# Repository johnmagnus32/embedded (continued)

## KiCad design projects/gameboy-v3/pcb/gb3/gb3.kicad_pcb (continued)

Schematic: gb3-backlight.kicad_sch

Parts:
C45: 2.2µF; C0805; LCSC C125847
C46: 4.7µF; C0603; LCSC C109456
C47: 220nF; C0402; LCSC C326590
D3: SS16; SMA_L4.3-W2.6-LS5.2-RD; LCSC C2481
L2: 10µH; IND-SMD_L4.0-W4.0_LQH44PN2R2MP0L; LCSC C135263
R38: RC0402FR-075R1L; R0402; LCSC C137955
R51: 100k; R0603; LCSC C14675
TP11: TestPoint; TestPoint_Pad_D1.5mm
U6: TPS61165DBVR; SOT-23-6_L2.9-W1.6-P0.95-LS2.8-BR; LCSC C58756

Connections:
/backlight/BL_COMP: C47.1, U6.5 (COMP)
/backlight/BL_SW: D3.2 (A), L2.2, U6.3 (SW)
BL_CTRL: R51.1, U6.2 (CTRL); also elsewhere on the board
BL_LED_N: R38.1, U6.6 (FB); also elsewhere on the board
BL_LED_P: C45.1, D3.1 (K), TP11.1; also elsewhere on the board
GND: C45.2, C46.2, C47.2, R38.2, R51.2, U6.4 (GND); also elsewhere on the board
SYS: C46.1, L2.1, U6.1 (VIN); also elsewhere on the board

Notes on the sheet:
backlight

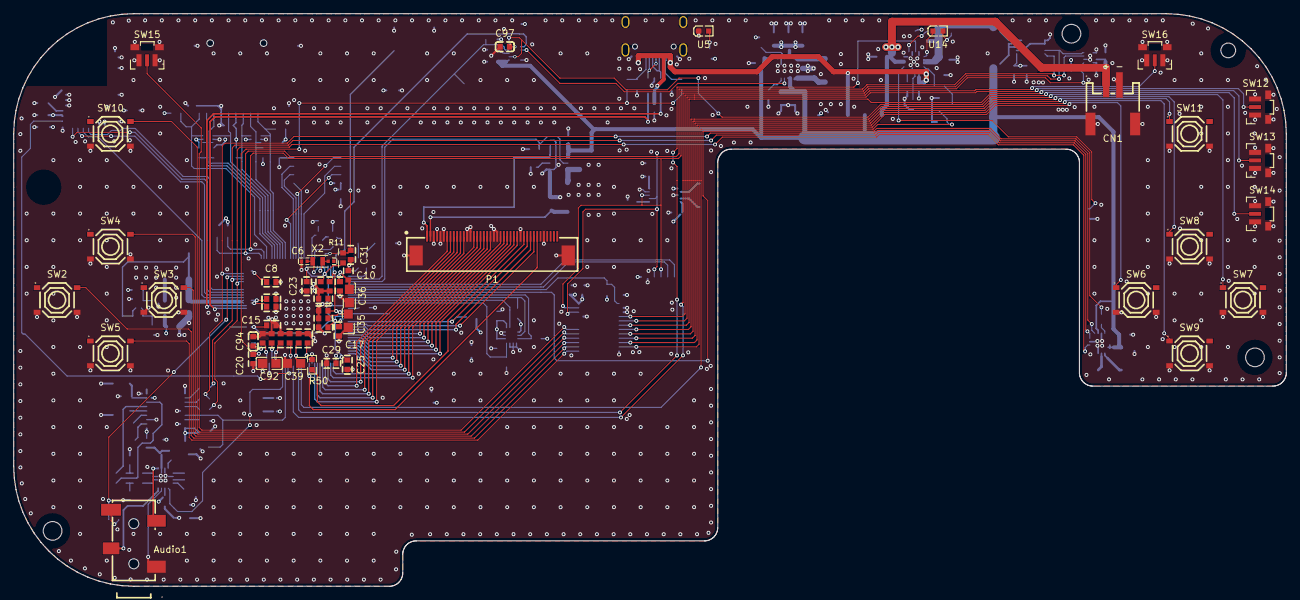
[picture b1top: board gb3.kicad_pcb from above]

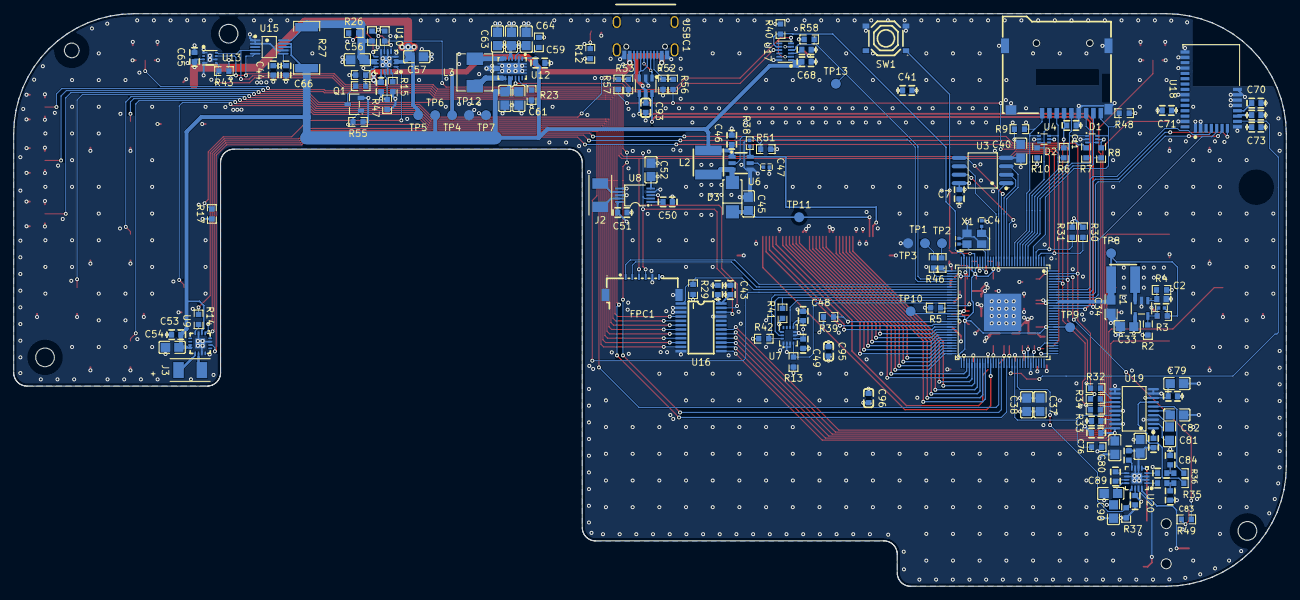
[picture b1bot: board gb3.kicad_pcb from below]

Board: 4 copper layers, 190.7 x 85.8 mm, 219 parts (159 on the bottom side), 157 nets.

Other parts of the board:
H1: MountingHole_2.2mm_M2; MountingHole_2.2x4.4mm_M2_slot
H2, H4, H5: MountingHole_2.2mm_M2; MountingHole_2.8mm_M2
H3: MountingHole_2.2mm_M2
LRA1: VG0832022D; LRA_VG0832022D
SPK1: CES-2704-088L050; SPEAKER_CES2704

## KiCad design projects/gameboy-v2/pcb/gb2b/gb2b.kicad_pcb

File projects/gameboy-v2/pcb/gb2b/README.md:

# gb2b: gb2 rev B

The KiCad project for **rev B** of gb2, the GBA-style handheld (STM32F411RE + iCE40UP5K driving the 8-bit 8080
display bus, BT830, BQ24073, TPS63021, MT3608). The design spec is **[../REVB_DESIGN.md](../REVB_DESIGN.md)**.

**Rev A (`../gb2/`) is ordered and frozen.** Never edit anything there. Rev B is a separate project that started
as a copy of it.

## What rev B changes (locked 2026-10-14)

- **Screen:** EastRising ER-TFT028A2-4 bare panel (2.8" IPS 240x320, ILI9341, no touch, 50-pin 0.5 mm FPC) replaces the
  Adafruit 2090 module. The panel is held in the front shell on a foam gasket under a 1.1 mm glass cover, with the board
  0.3 mm behind it. There are no front-side parts under the panel. The FPC folds behind the panel and joggles through a
  board opening to a top-contact 50-pin connector on the back (JUSHUO AFC07-S50ECA-00, LCSC C262650).
- **Battery:** Adafruit 258 (35 x 62 x 5 mm, 1200 mAh, JST-PH), in a portrait board cut-out left of that connector,
  behind a 0.5 mm stainless plate, with a flush battery door. The back is flat and the device is about 12.5 mm thick all round (REVB_DESIGN.md §3.1).
- **Extras:** USB D+/D- to the STM32 PA11/PA12 (DFU) with an ESD array and a VBUS TVS. J8 sits next to the charger U9.
  The IMU is kept away from screws, posts, the LRA and the speaker. The panel frame is grounded. TE goes to the FPGA
  (U2 pin 44, `LCD_TE`; REVB_DESIGN.md decision 16 moved it from the brief's pin 38 so the bus fans out without
  crossings). The FPGA drives the panel reset with a 10k pull-up. RD is tied to +3V3, IM0-3 and the unused
  inputs go to GND, and SDO is left open.

## Status

**Schematic: rev B's electrical changes are in (2026-10-14).** The PCB is not updated yet.

- `gb2b-nets.csv` / `gb2b-bom.csv` carry REVB_DESIGN.md §4-5:
  - the 50-pin FPC connector J3, with every panel pin wired;
  - the backlight driver (R32-R37, Q2; R32-R35 = 120 Ω C22787) on a new `backlight` sheet;
  - the LCD_RST pull-up R38, and C52/C53;
  - the GND pads MP1-MP8 (MP7/MP8 land the plate's copper-foil bridges);
  - USB D+/D- to PA11/PA12 through U13, with the VBUS TVS D4;
  - the right-angle SWD header J1, and the 10k reel swap;
  - the schematic-review fixes: FPGA_CDONE moved to PB0 with R39 pulling BOOT1 (PB2) low, and R25 as a PS/SYNC
    pull-up (REVB_DESIGN.md decisions 14 and 22).

  J4 is gone. BOM changes: `BOM_REVB.md`. `BOM.md` here is rev B's full machine-readable BOM (rev A's rows plus
  #84-#92), which `fab/fab.py` reads.
- The schematic regenerates with `gen.py` (below): 154 parts and 19 child sheets. The VALIDATE gate passes. ERC gives
  0 errors and 229 warnings, all of the same two kinds as rev A's 229: generator-made power symbols not found in the
  `power` library, and pin-to-pin warnings on the shared library's "unspecified" pins.
- `gb2b.kicad_pcb` is still rev A's placed and routed board, linked to the rev A parts. It still has J4 and the old J3,
  and it lacks the 21 new parts until "Update PCB from Schematic" (or `place.py`) runs in the placement step
  (REVB_DESIGN.md §9 step 3). `route/groups/` was deliberately **not** copied.
- These files still describe rev A and get revised as rev B lands:
  - `mech_ref.json` + `draw_mech.py` (the 2090 module and the Adafruit 2011 cell);
  - `route/PLAN.md` and `route/channels.py` (rev A's corridors);
  - `fab/verify.py` (checks J3/J4 against the 2090);
  - `fab/fab.py`'s checklist notes (J1, J3, J8). Its BOM lookup now reads `BOM.md` in this directory and stops on an
    unknown `#N`.

## Layout

| Path | What |
|---|---|
| `gb2b.kicad_pro` / `.kicad_sch` / `sheets/gb2b-*.kicad_sch` | Project + generated hierarchical schematic (one child sheet per subcircuit) |
| `gb2b.kicad_pcb`, `gb2b.kicad_dru` | Board + custom DRC rules |
| `gb2b-bom.csv`, `gb2b-nets.csv` | **The schematic source.** Edit these, never the .kicad_sch |
| `lib/gb2b.kicad_sym`, `lib/gb2b.pretty/`, `lib/gb2b.3dshapes/` | Project-local library (nickname `gb2b`) for rev B's new symbols and footprints. `../../../../cad/symbols` holds shared work, so rev B parts don't go there |
| `gen.py` | Runs the schematic generator with the project-local library |
| `BOM_REVB.md` | Rev B's BOM delta against rev A (LCSC, tier, stock) and the footprint checks |
| `BOM.md` | Rev B's full BOM rows (rev A's + #84-#92), the `#N` lookup `fab/fab.py` uses |
| `title.py` | Stamps the "gb2 rev B" title block into every sheet + the board |
| `place.py` | Schematic -> board import + placement |
| `route/` | Routing + check tools (fanout, pour, silk, audit, IPC current, I2C rise time, plane return path, plot) |
| `fab/fab.py`, `fab/verify.py` | JLC outputs (into `fab/out/`, git-ignored) + the pre-fab checks |

## Regenerating the schematic

Close KiCad first, then from the repo root:

```sh
python3 projects/gameboy-v2/pcb/gb2b/gen.py       # = cad/generate_schematic.py + the gb2b library, on this dir's CSVs
python3 projects/gameboy-v2/pcb/gb2b/title.py     # the generator writes no title block
```

`gen.py` wraps the shared generator without changing it. The generator itself only loads `easyeda2kicad` and `manual`
from one `--symbols` directory, so the wrapper also loads `lib/gb2b.kicad_sym`. Pass `--project <copy>` for a dry run
into a copy at the same folder depth.

The generator's VALIDATE gate (ERC 0 errors, netlist partition match) must say PASS.

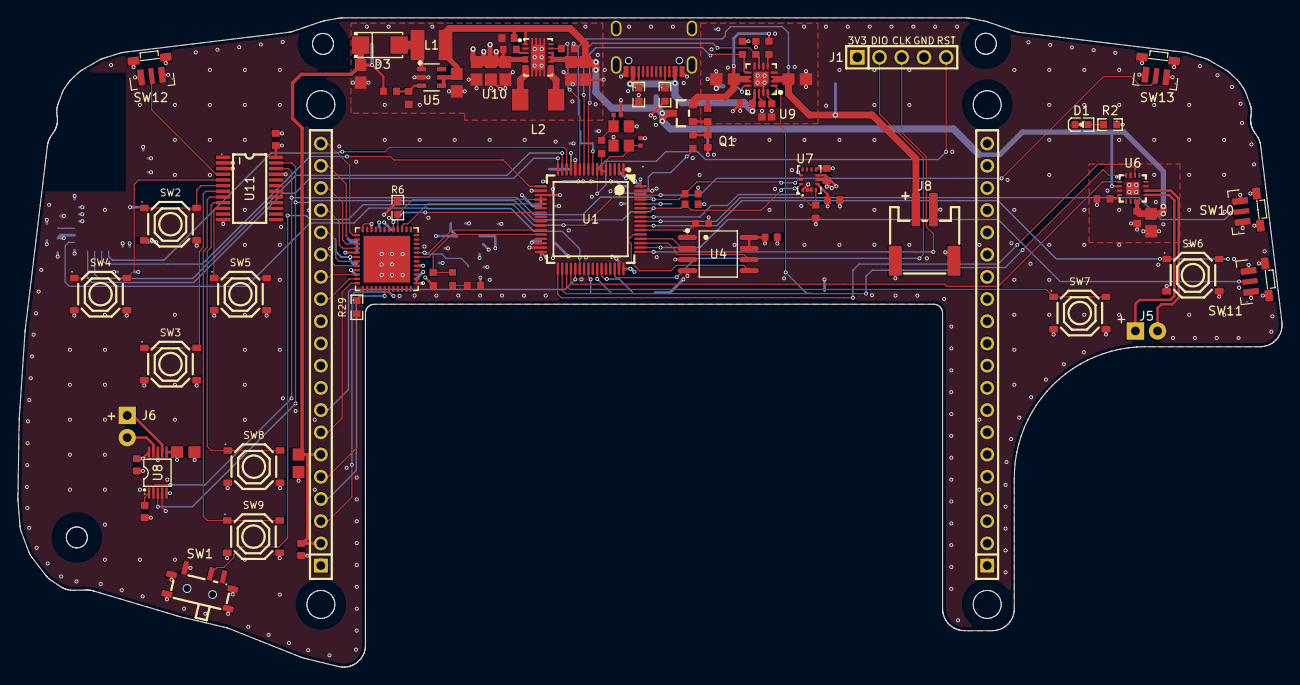
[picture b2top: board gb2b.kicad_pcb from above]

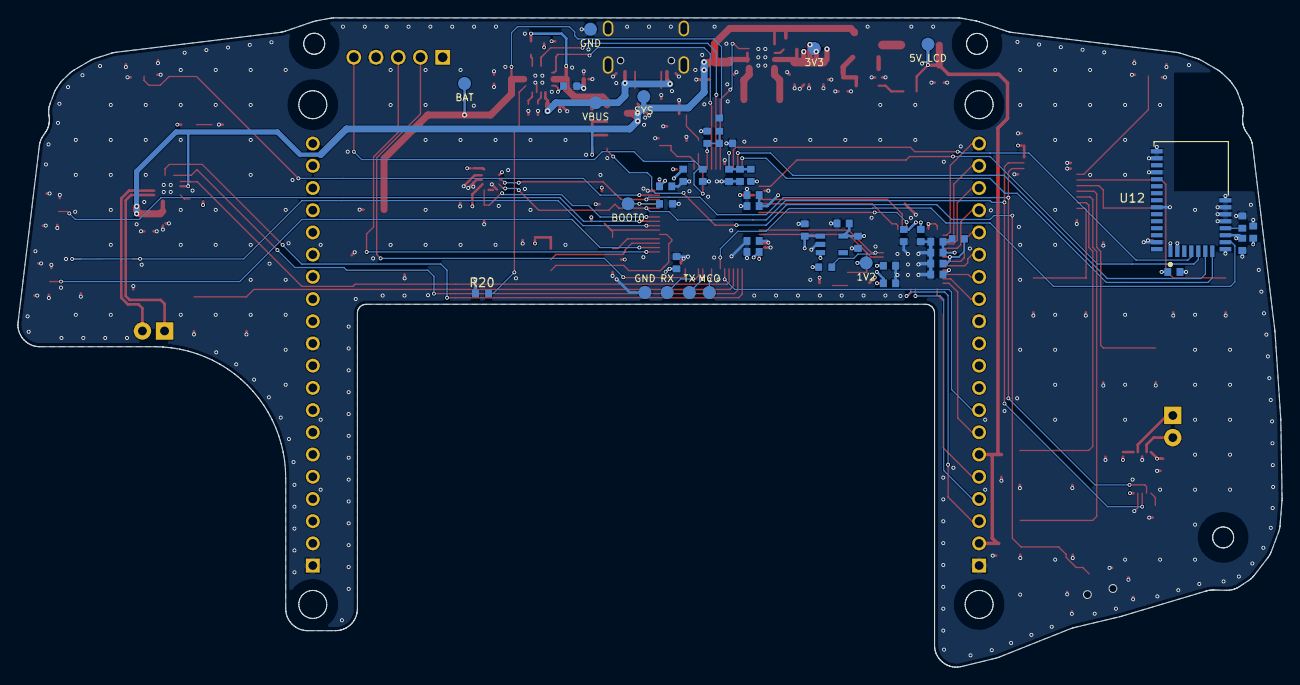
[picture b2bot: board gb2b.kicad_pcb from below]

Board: 4 copper layers, 144.6 x 74.2 mm, 134 parts (48 on the bottom side), 94 nets.

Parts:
C1, C2, C3, C4, C5, C6, C13, C14, C15, C16, C17, C18, C19, C24, C25, C29, C31, C32, C34, C39, C45, C46, C48, C49, C51: 100nF; C0603
C7, C8, C20, C21, C22, C23, C36, C47, C50: 4.7µF; C0603
C9: 10nF; C0603
C10, C33: 1µF; C0603
C11, C12: 15pF; C0402
C26, C27, C30, C35, C37, C38, C40, C41: 10µF; C0805
C28, C42, C43, C44: 22µF; C0805
D1, D2: 19-213SYGC/S530-E2/5T; LED0603-RD
D3: SS34_C8678; SMA_L4.3-W2.6-LS5.2-RD
FB1, FB2: 600Ω; L0603
J1: MTP125-1105S1; HDR-TH_5P-P2.54-V-M
J3, J4: HX PM2.54-1X20P ZC; PinSocket_1x20_P2.54_D1.0
J5, J6: SolderPad_1x02
J7: TYPE-C-31-M-12; USB-C_SMD-TYPE-C-31-M-12_1
J8: S2B-PH-SM4-TB; CONN-SMD_P2.00_S2B-PH-SM4-TB-LF-SN
L1: 4.7µH; IND-SMD_L4.0-W4.0
L2: 1.5µH; IND-SMD_L5.4-W5.2
Q1: AO3401A; SOT-23_L2.9-W1.3-P1.90-LS2.4-BR
R1, R4, R5, R8, R10, R12, R20, R22, R23, R31: 10k; R0603
R2, R7: 510Ω; R0603
R3, R17, R24: 0Ω; R0603
R6, R19: 3.3k; R0603
R9: 73.2k; R0603
R11: 620k; R0603
R13, R14: 1.5k; R0603
R15, R16: 5.1k; R0603
R18: 2k; R0603
R21: 68k; R0603
R25, R26, R27, R30: 100k; R0603
R29: 33Ω; R0603
SW1: MSK12C02-HB; SW-TH_MSK12C02-HB-1
SW2, SW3, SW4, SW5, SW6, SW7, SW8, SW9: TS-1187A-B-A-B; SW-SMD_4P-L5.1-W5.1-P3.70-LS6.5-TL_H1.5
SW10, SW11, SW12, SW13: SKRTLBE010; KEY-SMD_SKRTLAE010-1
TP1, TP2, TP3, TP4, TP5, TP6, TP7, TP8, TP9, TP10, TP11, TP12: TestPoint; TestPoint_Pad_D1.5mm
U1: STM32F411RET6; LQFP-64_L10.0-W10.0-P0.50-LS12.0-BL
U2: ICE40UP5K-SG48I; QFN-48_L7.0-W7.0-P0.50-TL-EP5.4-1
U3: AP2127K-1.2TRG1; SOT-23-5_L3.0-W1.7-P0.95-LS2.8-BR
U4: W25Q128JVSIQTR; SOIC-8_L5.3-W5.3-P1.27-LS8.0-BL
U5: MT3608; SOT-23-6_L2.9-W1.6-P0.95-LS2.8-BL
U6: MAX98357AETE+T; TQFN-16_L3.0-W3.0-P0.50-BL-EP1.5
U7: LSM6DSOXTR; LGA-14L_L3.0-W2.5-P0.50-TL
U8: DRV2605LDGSR; VSSOP-10_L3.0-W3.0-P0.50-LS4.9-BL
U9: BQ24073RGTR; QFN-16_L3.0-W3.0-P0.50-TL-EP1.7
U10: TPS63021DSJR; VSON-14_L4.0-W3.0-P0.50-BL-EP_TI_DSJ
U11: PCA9555PWR; TSSOP-24_L7.8-W4.4-P0.65-LS6.4-BL
U12: BT830-SA-01-T_R; XCVR_BT830-SA-01-T_R
Y1: DSX321G 8MHz; CRYSTAL-SMD_4P-L3.2-W2.5-BL-1

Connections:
+1V2: C13.1, C14.1, C22.1, C23.1, FB2.1, TP7.1, U2.5, U2.30, U3.5
+1V2_PLL: C19.1, C20.1, FB2.2, U2.29
+3V3: C1.1, C2.1, C3.1, C4.1, C5.1, C8.1, C15.1, C16.1, C17.1, C18.1, C21.1, C24.1, C31.1, C32.1, C34.1, C35.1, C42.1, C43.1, C44.1, C46.1, C48.1, C49.1, C50.1, FB1.1, J1.1, R2.1, R4.2, R5.2, R7.1, R8.2, R11.2, R13.2, R14.2, R22.2, R23.2, R24.2, TP5.1, U1.1, U1.19, U1.32, U1.48, U1.64, U2.1, U2.22, U2.24, U2.33, U3.1, U3.3, U4.3, U4.7, U4.8, U7.5, U7.8, U7.12, U8.5, U8.6, U8.10, U10.4, U10.5, U11.24, U12.1, U12.9
+3V3A: C9.1, C10.1, FB1.2, U1.13
+5V_LCD: C25.1, C26.1, C28.1, D3.1, J3.2, J3.6, R9.1, TP6.1
/amp/AMP_SD_MODE: R11.1, U6.4
/amp/SPK_N: J5.2, U6.10
/amp/SPK_P: J5.1, U6.9
/bluetooth/BT_VREG18: C47.1, U12.10
/buck-boost/BB_FB: R24.1, U10.3
/buck-boost/BB_L1: L2.1, U10.8, U10.9
/buck-boost/BB_L2: L2.2, U10.6, U10.7
/charger/CHG_EN2: R17.1, U9.5
/charger/CHG_ILIM: R19.1, U9.12
/charger/CHG_ISET: R18.1, U9.16
/charger/CHG_TMR: R21.1, U9.14
/charger/CHG_TS: R20.1, U9.1
/charger/PWR_SW: R31.1, SW1.2
/charger/Q1_GATE: C51.1, Q1.1, R30.1, R31.2
/clock/HSE_OUT: C12.1, R3.2, Y1.3
/fpga/CDONE_LED_A: D2.2, R7.2
/fpga/LCD_WR_FPGA: R29.1, U2.37
/haptics/HAP_REG: C33.1, U8.1
/haptics/LRA_N: J6.2, U8.9
/haptics/LRA_P: J6.1, U8.7
/lcd-boost/BST_FB: R9.2, R10.1, U5.3
/lcd-boost/BST_SW: D3.2, L1.2, U5.1
/mcu/BOOT0: R1.1, TP8.1, U1.60
/mcu/MCO2: TP9.1, U1.40
/mcu/NRST: C6.1, J1.5, U1.7
/mcu/PWR_LED_A: D1.2, R2.2
/mcu/SWCLK: J1.3, U1.49
/mcu/SWDIO: J1.2, U1.46
/mcu/USART1_RX: TP12.1, U1.43
/mcu/USART1_TX: TP11.1, U1.42
/mcu/VCAP1: C7.1, U1.30
/usb-c/USBC_CC1: J7.A5, R15.1
/usb-c/USBC_CC2: J7.B5, R16.1
BAT: C38.1, J8.1, R26.1, TP2.1, U9.2, U9.3
BAT_SENSE: C45.1, R26.2, R27.1, U1.8
BB_PSYNC: R25.1, U1.11, U10.13
BTN_A: SW6.1, SW6.2, U1.55
BTN_B: SW7.1, SW7.2, U1.35
BTN_DOWN: SW3.1, SW3.2, U11.7
BTN_L: SW12.2, U11.4
BTN_LEFT: SW4.1, SW4.2, U11.5
BTN_R: SW13.2, U1.62
BTN_RIGHT: SW5.1, SW5.2, U11.10
BTN_SELECT: SW9.1, SW9.2, U11.8
BTN_START: SW8.1, SW8.2, U11.9
BTN_UP: SW2.1, SW2.2, U11.6
BTN_VOLDOWN: SW11.2, U1.50
BTN_VOLUP: SW10.2, U1.56
BT_EN: U1.38, U12.8
CHG_PGOOD: R23.1, U1.10, U9.7
CHG_STAT: R22.1, U1.9, U9.9
FPGA_CDONE: D2.1, R5.1, U1.28, U2.7
FPGA_CRESET_B: R4.1, U1.27, U2.8
FPGA_SS_B: R6.1, U1.20, U2.16
GND: C1.2, C2.2, C3.2, C4.2, C5.2, C6.2, C7.2, C8.2, C9.2, C10.2, C11.2, C12.2, C13.2, C14.2, C15.2, C16.2, C17.2, C18.2, C19.2, C20.2, C21.2, C22.2, C23.2, C24.2, C25.2, C26.2, C27.2, C28.2, C29.2, C30.2, C31.2, C32.2, C33.2, C34.2, C35.2, C36.2, C37.2, C38.2, C39.2, C40.2, C41.2, C42.2, C43.2, C44.2, C45.2, C46.2, C47.2, C48.2, C49.2, C50.2, D1.1, J1.4, J3.1, J3.12, J4.1, J4.11, J7.1, J7.2, J7.3, J7.4, J7.A1B12, J7.B1A12, J8.2, J8.3, J8.4, R1.2, R6.2, R10.2, R12.2, R15.2, R16.2, R18.2, R19.2, R20.2, R21.2, R25.2, R27.2, SW1.1, SW1.4, SW2.3, SW2.4, SW3.3, SW3.4, SW4.3, SW4.4, SW5.3, SW5.4, SW6.3, SW6.4, SW7.3, SW7.4, SW8.3, SW8.4, SW9.3, SW9.4, SW10.1, SW10.3, SW10.4, SW10.5, SW11.1, SW11.3, SW11.4, SW11.5, SW12.1, SW12.3, SW12.4, SW12.5, SW13.1, SW13.3, SW13.4, SW13.5, TP4.1, TP10.1, U1.12, U1.18, U1.31, U1.47, U1.63, U2.49, U3.2, U4.4, U5.2, U6.3, U6.11, U6.15, U6.17, U7.1, U7.2, U7.3, U7.6, U7.7, U8.4, U8.8, U9.4, U9.6, U9.8, U9.15, U9.17, U10.2, U10.15, U11.2, U11.3, U11.12, U11.21, U12.2, U12.11, U12.12, U12.13, U12.14, U12.15, U12.16, U12.18, U12.23, U12.28, U12.30, Y1.2, Y1.4
HSE_IN: C11.1, U1.5, Y1.1
HSE_OUT_MCU: R3.1, U1.6
I2C1_SCL: R13.1, U1.61, U7.13, U8.2, U11.22
I2C1_SDA: R14.1, U1.59, U7.14, U8.3, U11.23
I2S2_CK: U1.34, U6.16
I2S2_SD: U1.36, U6.1
I2S2_WS: U1.33, U6.14
IMU_INT1: R12.1, U1.57, U7.4
LCD_CS: J3.3, U2.43
LCD_D0: J3.13, U2.35
LCD_D1: J3.14, U2.34
LCD_D2: J3.15, U2.32
LCD_D3: J3.16, U2.31
LCD_D4: J3.17, U2.28
LCD_D5: J3.18, U2.27
LCD_D6: J3.19, U2.26
LCD_D7: J3.20, U2.25
LCD_DC: J3.4, U2.42
LCD_LITE: J3.8, U1.37
LCD_RST: J3.7, U2.36
LCD_WR: J3.5, R29.2
NOR_CS: R8.1, U1.54, U4.1
PPU_SPI_MOSI: U1.23, U2.17
PPU_SPI_SCK: U1.21, U2.15
SPI3_MISO: U1.52, U4.2
SPI3_MOSI: U1.53, U4.5
SPI3_SCK: U1.51, U4.6
SYS: C27.1, C29.1, C30.1, C39.1, C40.1, C41.1, C51.2, L1.1, Q1.3, TP3.1, U5.4, U5.5, U6.2, U6.7, U6.8, U10.1, U10.10, U10.11, U10.12
SYS_SRC: C37.1, Q1.2, R17.2, R30.2, U9.10, U9.11
USART2_CTS: U1.14, U12.4
USART2_RTS: U1.15, U12.6
USART2_RX: U1.17, U12.5
USART2_TX: U1.16, U12.7
VBUS: C36.1, J7.A4B9, J7.B4A9, TP1.1, U9.13

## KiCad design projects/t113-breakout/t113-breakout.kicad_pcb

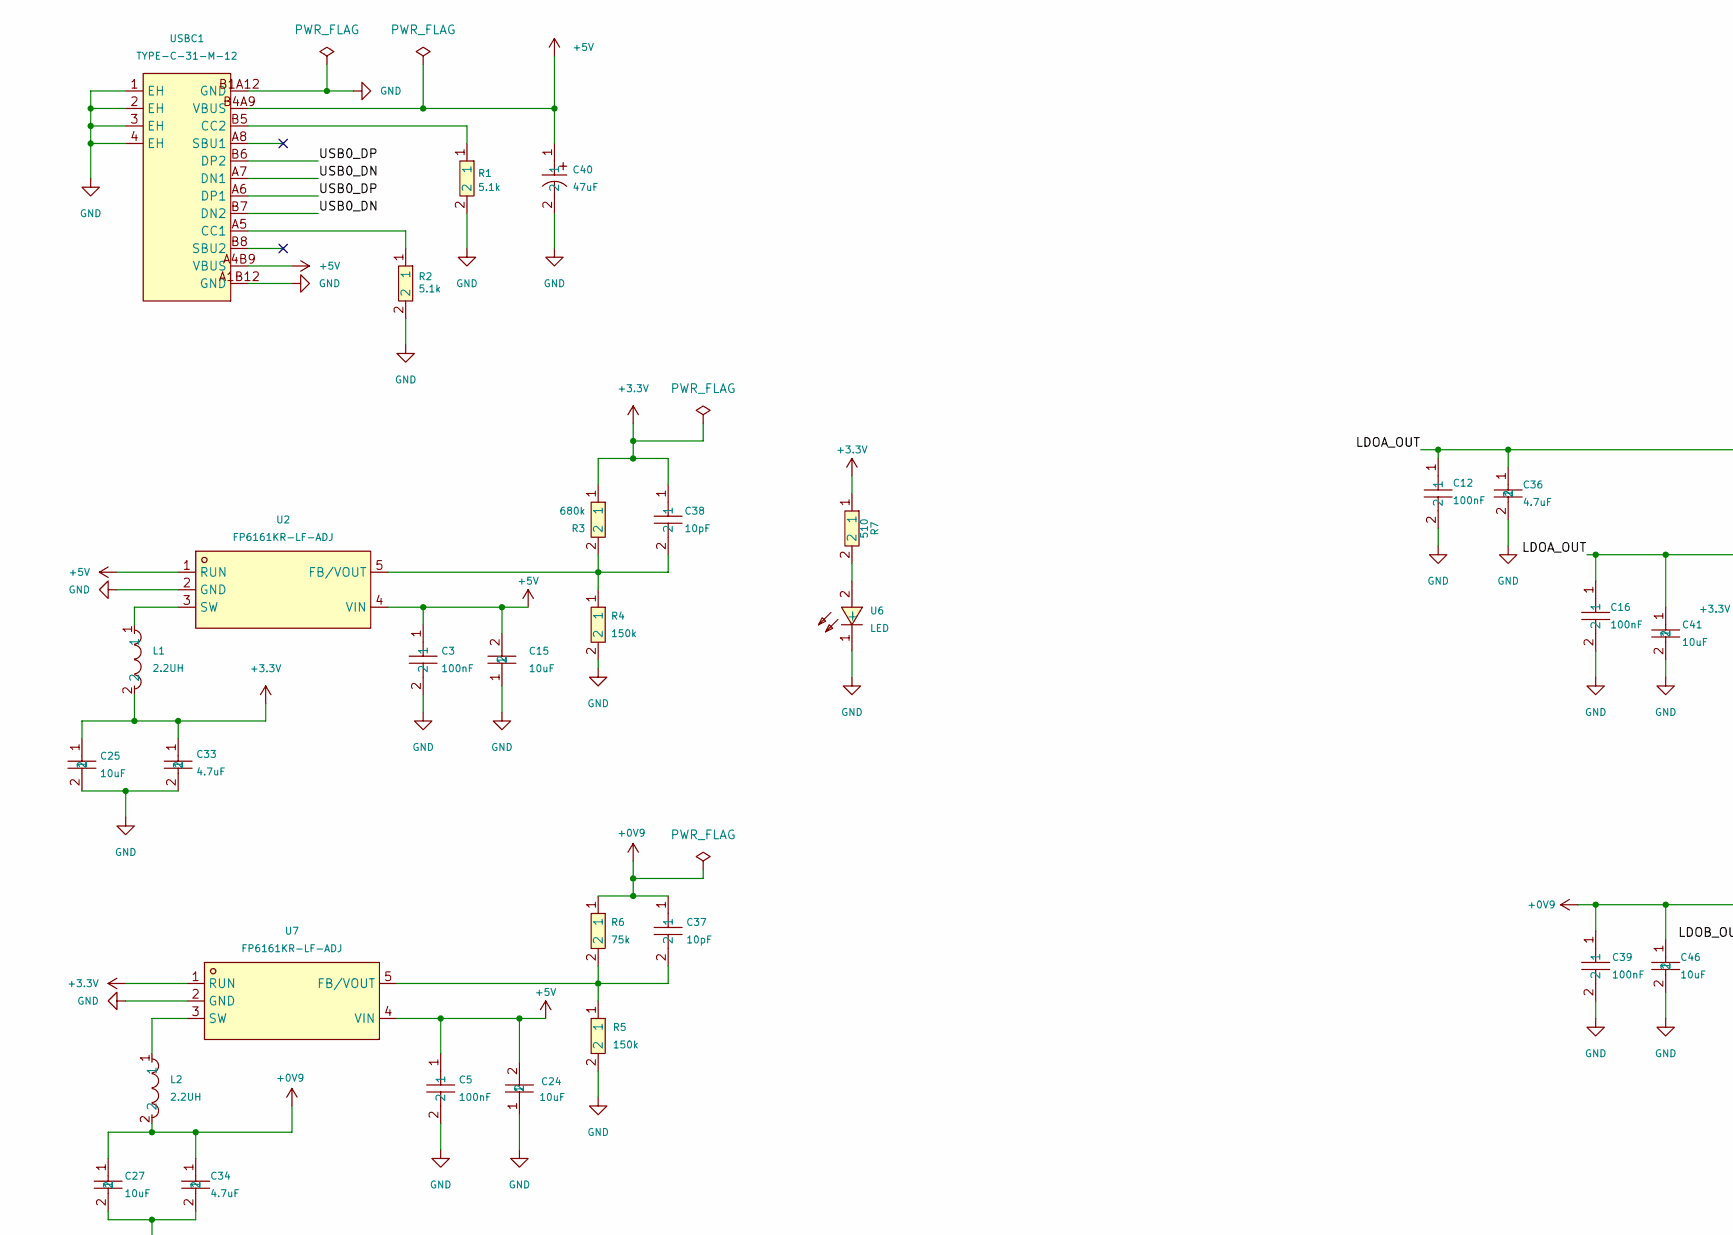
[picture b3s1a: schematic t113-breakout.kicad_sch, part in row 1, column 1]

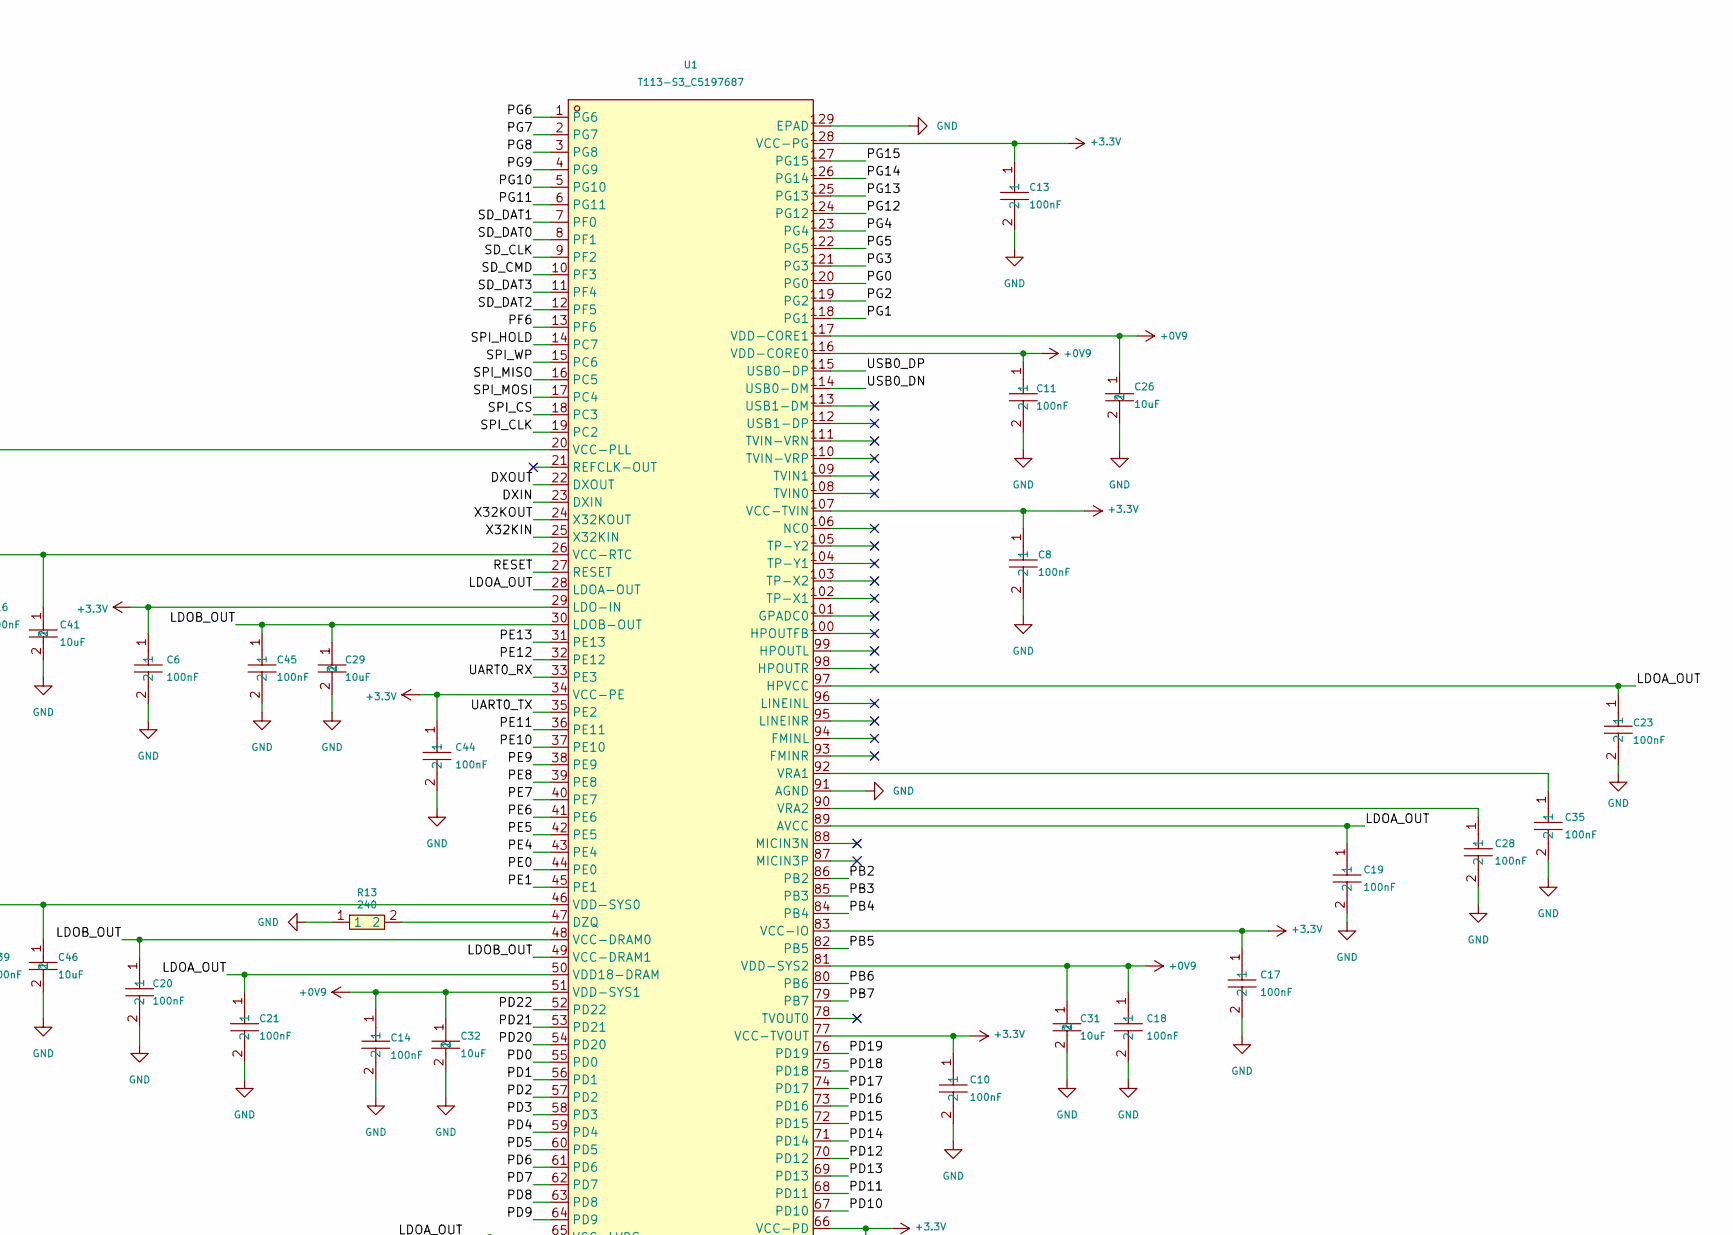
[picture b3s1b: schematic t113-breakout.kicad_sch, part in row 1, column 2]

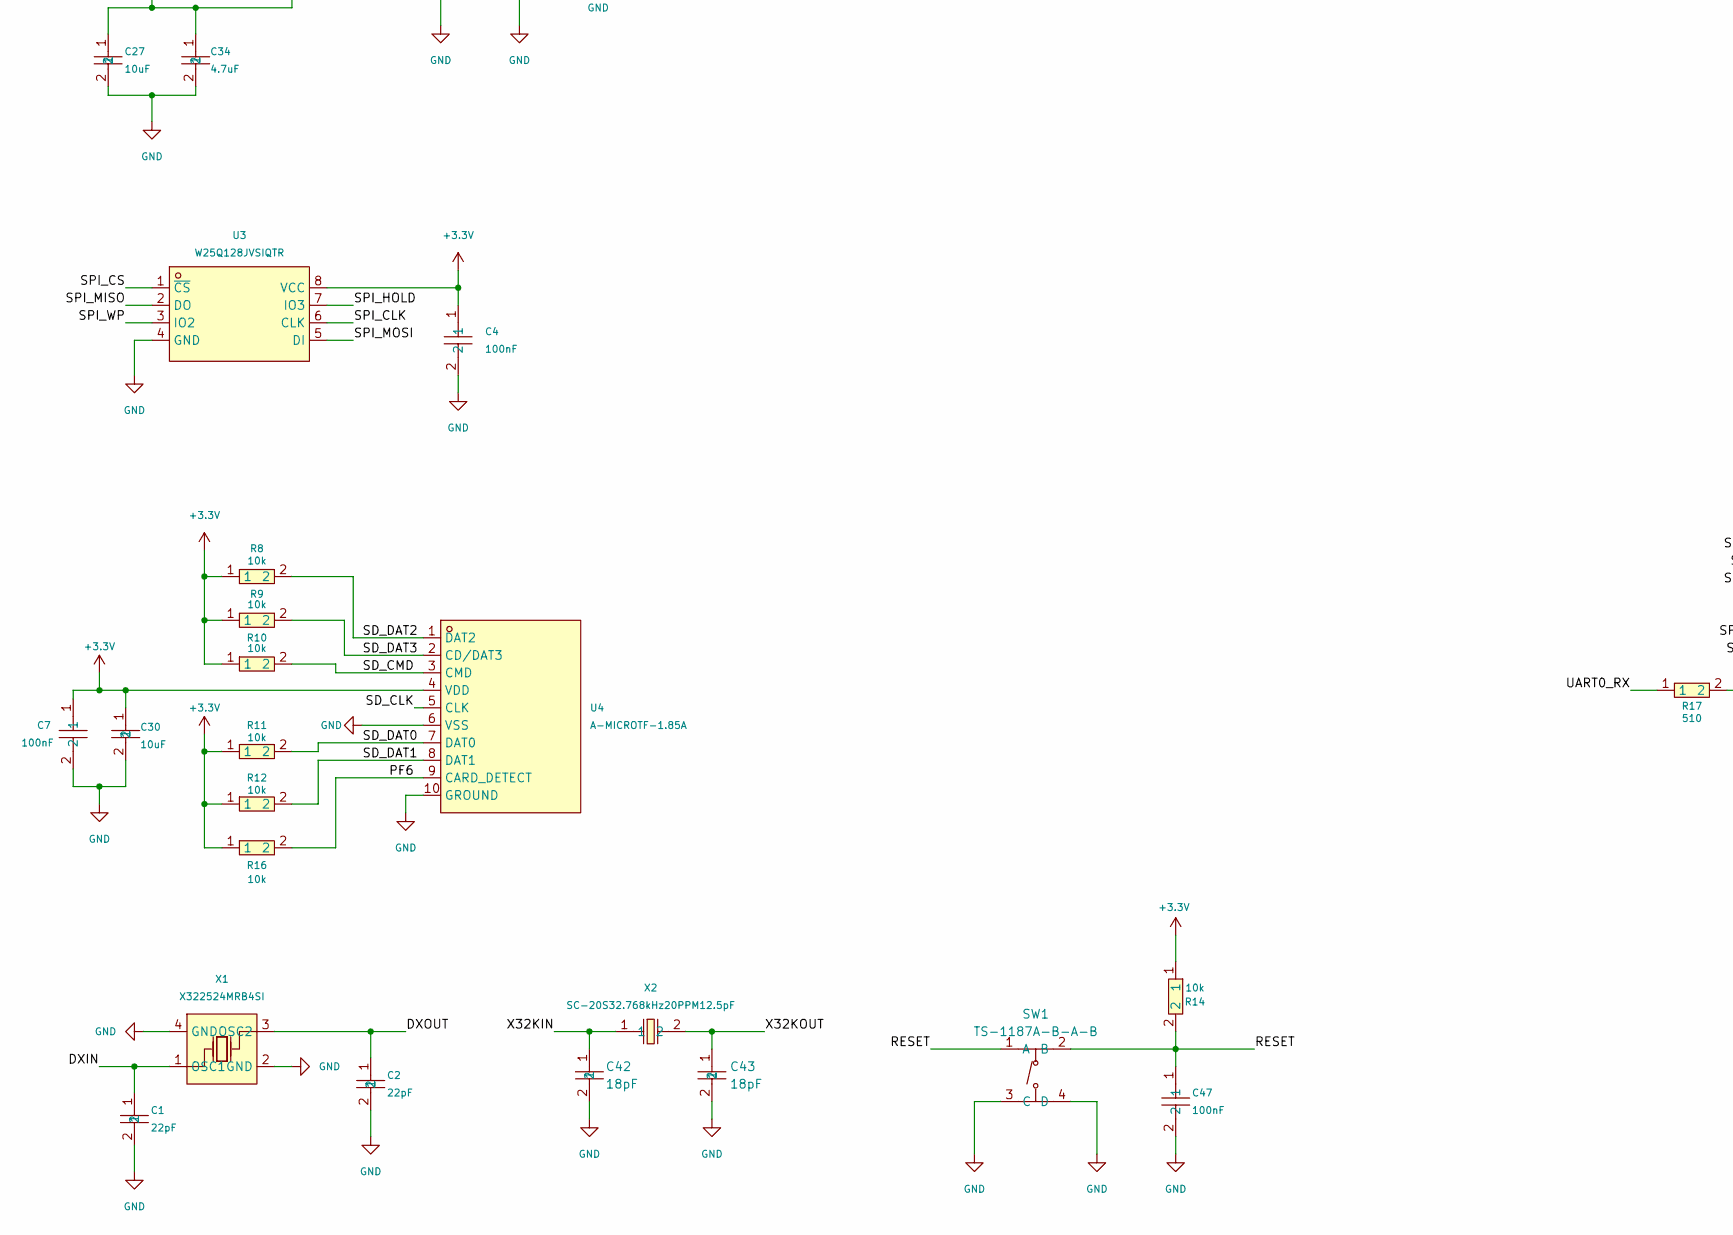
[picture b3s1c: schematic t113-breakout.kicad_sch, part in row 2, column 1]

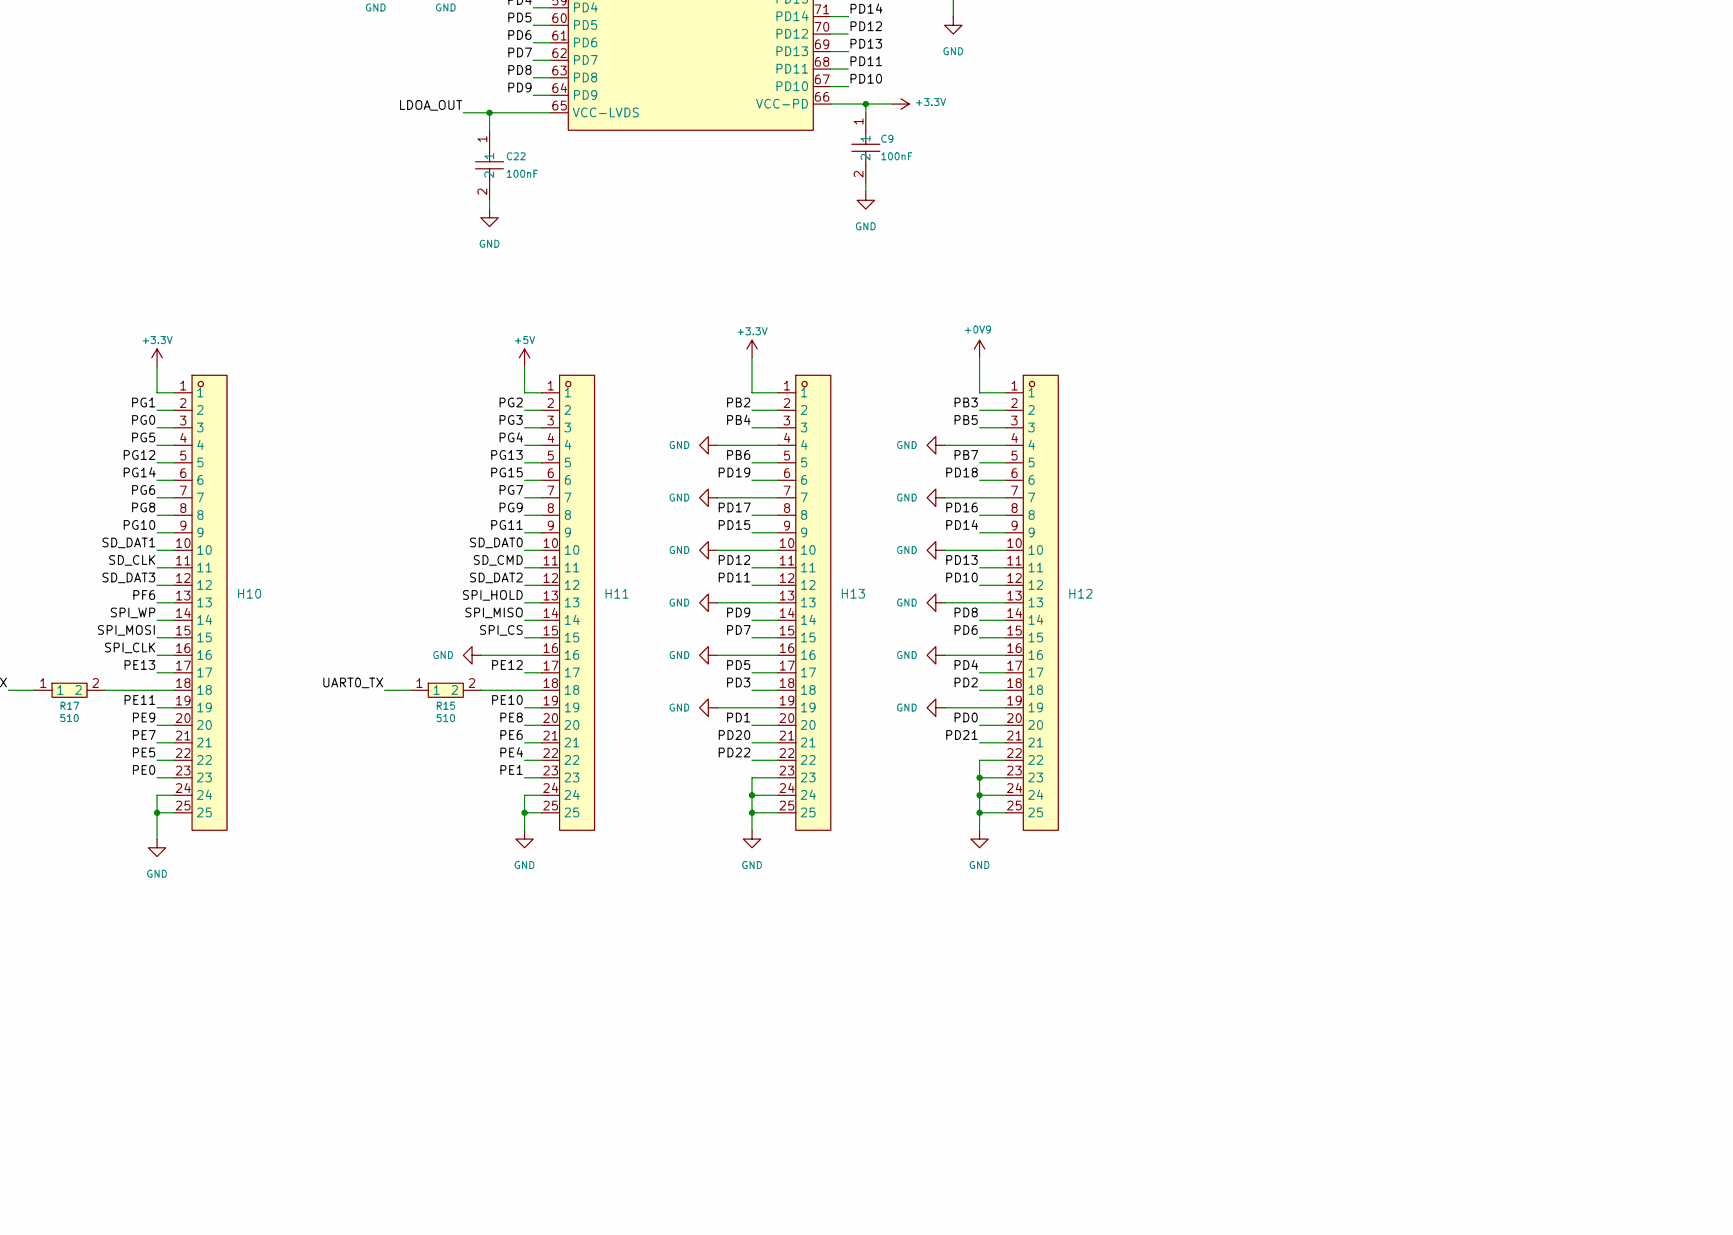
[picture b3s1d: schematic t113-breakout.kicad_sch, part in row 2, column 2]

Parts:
C1, C2: 22pF; C0402; MPN 0402CG220J500NT; LCSC Part C1555
C3, C4, C5, C6, C7, C8, C9, C10, C11, C12, C13, C14, C16, C17, C18, C19, C20, C21, C22, C23, C28, C35, C39, C44, C45, C47: 100nF; C0603; MPN CC0603KRX7R9BB104; LCSC Part C14663
C15, C24, C25, C26, C27, C29, C30, C31, C32, C41, C46: 10uF; C0805; MPN CL21A106KOQNNNE; LCSC Part C1713
C33, C34, C36: 4.7uF; C0603; MPN CC0603KRX5R6BB475; LCSC Part C109456
C37, C38: 10pF; C0402; MPN CL05C100JB5NNNC; LCSC Part C32949
C40: 47uF; CAP-SMD_BD6.3-L6.6-W6.6-LS7.2-FD; MPN RVT1E470M0605 47UF 25V; LCSC Part C970677
C42, C43: 18pF; C0402; MPN 0402CG180J500NT; LCSC Part C1549
H10, H11, H12, H13: 2044-1X25G00SA; HDR-TH_25P-P2.54-V-F_2044-1X25G00SA; MPN 2044-1X25G00SA; LCSC Part C49569761
L1, L2: 2.2UH; IND-SMD_L4.0-W4.0_LQH44PN2R2MP0L; MPN SMNR4020-2.2UH; LCSC Part C135262
R1, R2: 5.1k; R0603; MPN RC0603FR-075K1L; LCSC Part C105580
R3: 680k; R0603; MPN RS-03K6803FT; LCSC Part C140074
R4, R5: 150k; R0603; MPN 0603WAF1503T5E; LCSC Part C22807
R6: 75k; R0603; MPN 0603WAF7502T5E; LCSC Part C23242
R7, R15, R17: 510; R0603; MPN 0603WAF5100T5E; LCSC Part C23193
R8, R9, R10, R11, R12, R14, R16: 10k; R0603; MPN RC0603JR-0710KL; LCSC Part C99198
R13: 240; R0603; MPN 0603WAF2400T5E; LCSC Part C23350
SW1: TS-1187A-B-A-B; SW-SMD_4P-L5.1-W5.1-P3.70-LS6.5-TL_H1.5; MPN TS-1187A-B-A-B; LCSC Part C318884
U1: T113-S3_C5197687; LQFP-128_L14.0-W14.0-P0.40-LS16.0-BL-EP5.6; MPN T113-S3; LCSC Part C5197687
U2, U7: FP6161KR-LF-ADJ; SOT-23-5_L3.0-W1.7-P0.95-LS2.8-BL; MPN FP6161KR-LF-ADJ; LCSC Part C77234
U3: W25Q128JVSIQTR; SOIC-8_L5.3-W5.3-P1.27-LS8.0-BL; MPN W25Q128JVSIQ; LCSC Part C97521
U4: A-MICROTF-1.85A; TF-SMD_A-MICROTF-1.85A; MPN A-MicroTF-1.85A; LCSC Part C22467599
U6: LED; LED0603-RD; MPN 19-213SYGC/S530-E2/5T; LCSC Part C2986027
USBC1: TYPE-C-31-M-12; USB-C_SMD-TYPE-C-31-M-12_1; MPN TYPE-C-31-M-12; LCSC Part C165948
X1: X322524MRB4SI; CRYSTAL-SMD_4P-L3.2-W2.5-BL-2; MPN X322524MRB4SI; LCSC Part C70571
X2: SC-20S32.768kHz20PPM12.5pF; OSC-SMD_L2.0-W1.2; MPN SC-20S,32.768kHz,20PPM,12.5pF; LCSC Part C97607

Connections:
+0V9: C11.1, C14.1, C18.1, C26.1, C27.1, C31.1, C32.1, C34.1, C37.1, C39.1, C46.1, H12.1, L2.2, R6.1, U1.46 (VDD-SYS0), U1.51 (VDD-SYS1), U1.81 (VDD-SYS2), U1.116 (VDD-CORE0), U1.117 (VDD-CORE1)
+3.3V: C4.1, C6.1, C7.1, C8.1, C9.1, C10.1, C13.1, C17.1, C25.1, C30.1, C33.1, C38.1, C44.1, H10.1, H13.1, L1.2, R3.1, R7.1, R8.1, R9.1, R10.1, R11.1, R12.1, R14.1, R16.1, U1.29 (LDO-IN), U1.34 (VCC-PE), U1.66 (VCC-PD), U1.77 (VCC-TVOUT), U1.83 (VCC-IO), U1.107 (VCC-TVIN), U1.128 (VCC-PG), U3.8 (VCC), U4.4 (VDD), U7.1 (RUN)
+5V: C3.1, C5.1, C15.2, C24.2, C40.1, H11.1, U2.1 (RUN), U2.4 (VIN), U7.4 (VIN), USBC1.A4B9 (VBUS), USBC1.B4A9 (VBUS)
/DXIN: C1.1, U1.23 (DXIN), X1.1 (OSC1)
/DXOUT: C2.1, U1.22 (DXOUT), X1.3 (OSC2)
/LDOA_OUT: C12.1, C16.1, C19.1, C21.1, C22.1, C23.1, C36.1, C41.1, U1.20 (VCC-PLL), U1.26 (VCC-RTC), U1.28 (LDOA-OUT), U1.50 (VDD18-DRAM), U1.65 (VCC-LVDS), U1.89 (AVCC), U1.97 (HPVCC)
/LDOB_OUT: C20.1, C29.1, C45.1, U1.30 (LDOB-OUT), U1.48 (VCC-DRAM0), U1.49 (VCC-DRAM1)
/PB2: H13.2, U1.86 (PB2)
/PB3: H12.2, U1.85 (PB3)
/PB4: H13.3, U1.84 (PB4)
/PB5: H12.3, U1.82 (PB5)
/PB6: H13.5, U1.80 (PB6)
/PB7: H12.5, U1.79 (PB7)
/PD0: H12.20, U1.55 (PD0)
/PD1: H13.20, U1.56 (PD1)
/PD2: H12.18, U1.57 (PD2)
/PD3: H13.18, U1.58 (PD3)
/PD4: H12.17, U1.59 (PD4)
/PD5: H13.17, U1.60 (PD5)
/PD6: H12.15, U1.61 (PD6)
/PD7: H13.15, U1.62 (PD7)
/PD8: H12.14, U1.63 (PD8)
/PD9: H13.14, U1.64 (PD9)
/PD10: H12.12, U1.67 (PD10)
/PD11: H13.12, U1.68 (PD11)
/PD12: H13.11, U1.70 (PD12)
/PD13: H12.11, U1.69 (PD13)
/PD14: H12.9, U1.71 (PD14)
/PD15: H13.9, U1.72 (PD15)
/PD16: H12.8, U1.73 (PD16)
/PD17: H13.8, U1.74 (PD17)
/PD18: H12.6, U1.75 (PD18)
/PD19: H13.6, U1.76 (PD19)
/PD20: H13.21, U1.54 (PD20)
/PD21: H12.21, U1.53 (PD21)
/PD22: H13.22, U1.52 (PD22)
/PE0: H10.23, U1.44 (PE0)
/PE1: H11.23, U1.45 (PE1)
/PE4: H11.22, U1.43 (PE4)
/PE5: H10.22, U1.42 (PE5)
/PE6: H11.21, U1.41 (PE6)
/PE7: H10.21, U1.40 (PE7)
/PE8: H11.20, U1.39 (PE8)
/PE9: H10.20, U1.38 (PE9)
/PE10: H11.19, U1.37 (PE10)
/PE11: H10.19, U1.36 (PE11)
/PE12: H11.17, U1.32 (PE12)
/PE13: H10.17, U1.31 (PE13)
/PF6: H10.13, R16.2, U1.13 (PF6), U4.9 (CARD_DETECT)
/PG0: H10.3, U1.120 (PG0)
/PG1: H10.2, U1.118 (PG1)
/PG2: H11.2, U1.119 (PG2)
/PG3: H11.3, U1.121 (PG3)
/PG4: H11.4, U1.123 (PG4)
/PG5: H10.4, U1.122 (PG5)
/PG6: H10.7, U1.1 (PG6)
/PG7: H11.7, U1.2 (PG7)
/PG8: H10.8, U1.3 (PG8)
/PG9: H11.8, U1.4 (PG9)
/PG10: H10.9, U1.5 (PG10)
/PG11: H11.9, U1.6 (PG11)
/PG12: H10.5, U1.124 (PG12)
/PG13: H11.5, U1.125 (PG13)
/PG14: H10.6, U1.126 (PG14)
/PG15: H11.6, U1.127 (PG15)
/RESET: C47.1, R14.2, SW1.1 (A), SW1.2 (B), U1.27 (RESET)
/SD_CLK: H10.11, U1.9 (PF2), U4.5 (CLK)
/SD_CMD: H11.11, R10.2, U1.10 (PF3), U4.3 (CMD)
/SD_DAT0: H11.10, R11.2, U1.8 (PF1), U4.7 (DAT0)
/SD_DAT1: H10.10, R12.2, U1.7 (PF0), U4.8 (DAT1)
/SD_DAT2: H11.12, R8.2, U1.12 (PF5), U4.1 (DAT2)
/SD_DAT3: H10.12, R9.2, U1.11 (PF4), U4.2 (CD/DAT3)
/SPI_CLK: H10.16, U1.19 (PC2), U3.6 (CLK)
/SPI_CS: H11.15, U1.18 (PC3), U3.1 (~CS)
/SPI_HOLD: H11.13, U1.14 (PC7), U3.7 (IO3)
/SPI_MISO: H11.14, U1.16 (PC5), U3.2 (DO)
/SPI_MOSI: H10.15, U1.17 (PC4), U3.5 (DI)
/SPI_WP: H10.14, U1.15 (PC6), U3.3 (IO2)
/UART0_RX: R17.1, U1.33 (PE3)
/UART0_TX: R15.1, U1.35 (PE2)
/USB0_DN: U1.114 (USB0-DM), USBC1.A7 (DN1), USBC1.B7 (DN2)
/USB0_DP: U1.115 (USB0-DP), USBC1.A6 (DP1), USBC1.B6 (DP2)
/X32KIN: C42.1, U1.25 (X32KIN), X2.1
/X32KOUT: C43.1, U1.24 (X32KOUT), X2.2
GND: C1.2, C2.2, C3.2, C4.2, C5.2, C6.2, C7.2, C8.2, C9.2, C10.2, C11.2, C12.2, C13.2, C14.2, C15.1, C16.2, C17.2, C18.2, C19.2, C20.2, C21.2, C22.2, C23.2, C24.1, C25.2, C26.2, C27.2, C28.2, C29.2, C30.2, C31.2, C32.2, C33.2, C34.2, C35.2, C36.2, C39.2, C40.2, C41.2, C42.2, C43.2, C44.2, C45.2, C46.2, C47.2, H10.24, H10.25, H11.16, H11.24, H11.25, H12.4, H12.7, H12.10, H12.13, H12.16, H12.19, H12.22, H12.23, H12.24, H12.25, H13.4, H13.7, H13.10, H13.13, H13.16, H13.19, H13.23, H13.24, H13.25, R1.2, R2.2, R4.2, R5.2, R13.1, SW1.3 (C), SW1.4 (D), U1.91 (AGND), U1.129 (EPAD), U2.2 (GND), U3.4 (GND), U4.6 (VSS), U4.10 (GROUND), U6.1 (-), U7.2 (GND), USBC1.1 (EH), USBC1.2 (EH), USBC1.3 (EH), USBC1.4 (EH), USBC1.A1B12 (GND), USBC1.B1A12 (GND), X1.2 (GND), X1.4 (GND)
unnamed: H10.18, R17.2
unnamed: H11.18, R15.2
unnamed: R13.2, U1.47 (DZQ)
unnamed: C35.1, U1.92 (VRA1)
unnamed: C28.1, U1.90 (VRA2)
unnamed: C38.2, R3.2, R4.1, U2.5 (FB/VOUT)
unnamed: L1.1, U2.3 (SW)
unnamed: R7.2, U6.2 (+)
unnamed: C37.2, R5.1, R6.2, U7.5 (FB/VOUT)
unnamed: L2.1, U7.3 (SW)
unnamed: R2.1, USBC1.A5 (CC1)
unnamed: R1.1, USBC1.B5 (CC2)
